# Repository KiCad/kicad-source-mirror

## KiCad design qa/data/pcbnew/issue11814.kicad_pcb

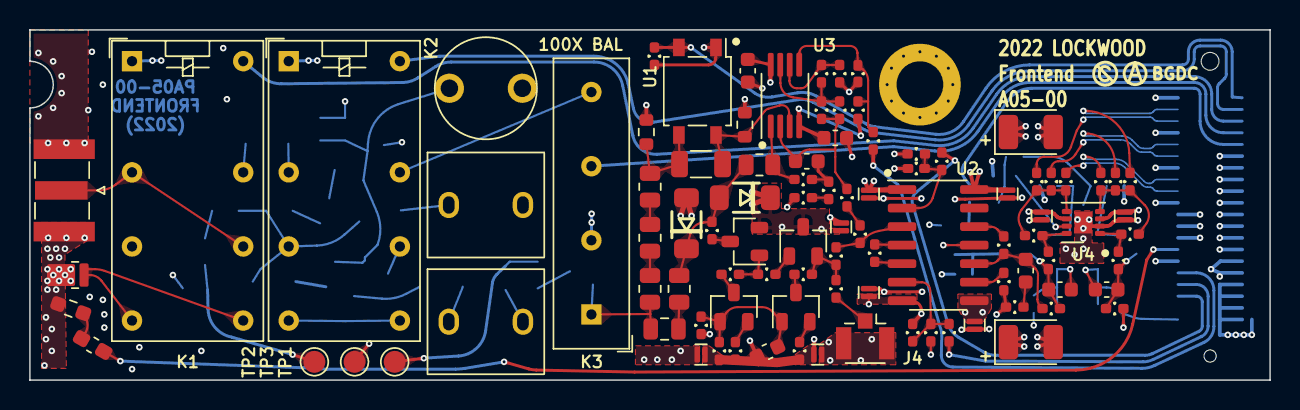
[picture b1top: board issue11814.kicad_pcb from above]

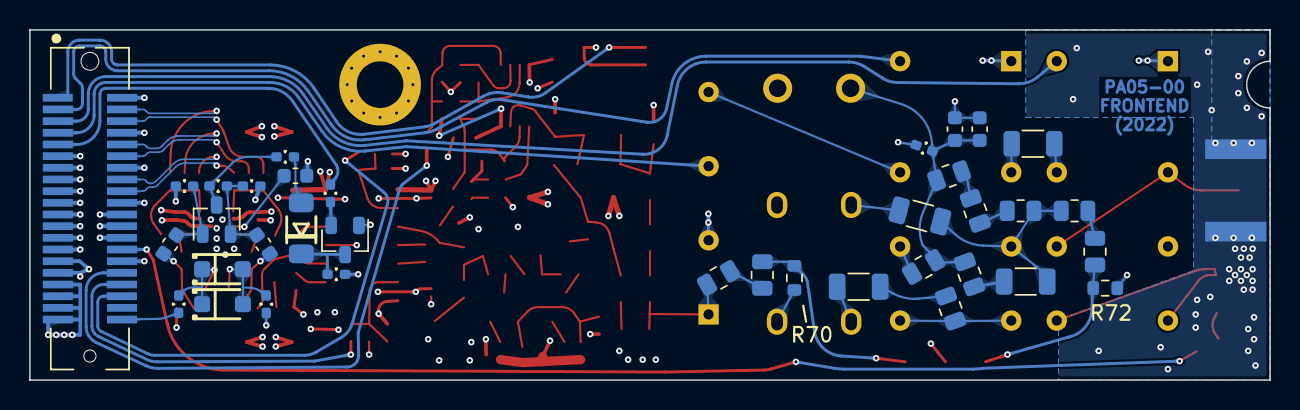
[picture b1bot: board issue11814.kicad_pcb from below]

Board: 4 copper layers, 85.0 x 24.0 mm, 133 parts (36 on the bottom side), 89 nets.

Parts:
C1, C7: 100n; C_0402_1005Metric_Pad0.74x0.62mm_HandSolder
C2, C4: 10p; C_1206_3216Metric
C3, C5: 2-18p; C-Trim-Vishay-BFC2-809-05
C6: 6p8; C_1206_3216Metric
C8: 15n; C_1206_3216Metric
C9: DNS; C_0603_1608Metric
C10: 560p; C_0603_1608Metric
C11: 62p; C_0603_1608Metric
C12, C18: 220p; C_0603_1608Metric
C13, C14: 47p; C_0603_1608Metric
C15: 15-60p; TrimCap-Generic
C16: 10n; C_0603_1608Metric
C17: 330p; C_0805_2012Metric
C19: 100p; C_0603_1608Metric
C28, C30: 47µ; CP_EIA-3528-15_AVX-H
C31, C32, C33: 100n; C_0603_1608Metric
CW1, CW2, CW3, CW4, CW5, CW6, CW7, CW8, CW9: 100n; C_0204_LowESL
D1, D5: 1N4007FL; D_SOD-123F
D2, D3, D4: LL4448; D_MiniMELF
FB1: 1k; L_0603_1608Metric_Pad1.05x0.95mm_HandSolder
H1: MountingHole_Pad; MountingHole_3.2mm_M3_DIN965_Pad
J1: Conn_Coaxial; SMA_Samtec_SMA-J-P-X-ST-EM1_EdgeMount
J3: INTERFACE; BergStak-Lite-40p-Receptacle
J4: TEST1; U.FL_Hirose_U.FL-R-SMT-1_Vertical
K1, K2: Relay-DPDT-CIT-J104D; Relay_DPDT_Omron_G5V-2
K3: Relay-SPST-Reed; Relay_SPST_StandexMeder_SIL_Form1A
Q1: MMBT3906; SOT-23
Q2: MMBFJ211; SOT-23
Q3: 2SK3557-7; SOT-23
Q4, Q5, Q6: MMBTH10; SOT-23
R1: 3k9; R_0402_1005Metric_Pad0.72x0.64mm_HandSolder
R2: 50; R_Susumu_HPT2012
R3, R5, R13: 30k; R_0402_1005Metric_Pad0.72x0.64mm_HandSolder
R7, R14: 120k; R_0402_1005Metric_Pad0.72x0.64mm_HandSolder
R8: 270; R_0402_1005Metric_Pad0.72x0.64mm_HandSolder
R9: 4R7; R_1206_3216Metric
R10: 18; R_0402_1005Metric_Pad0.72x0.64mm_HandSolder
R11: 18; R_0805_2012Metric
R12, R15, R18: 390k; R_0805_2012Metric
R16, R28: 390k; R_0603_1608Metric
R17, R51: 22; R_0805_2012Metric
R19, R24, R27: 330k; R_0805_2012Metric
R20, R54: 22; R_0402_1005Metric_Pad0.72x0.64mm_HandSolder
R21: 402; R_0402_1005Metric_Pad0.72x0.64mm_HandSolder
R22: 11k8; R_0402_1005Metric_Pad0.72x0.64mm_HandSolder
R23, R71, R74, R75: 3M; R_0805_2012Metric
R25, R37: DNS; R_0402_1005Metric_Pad0.72x0.64mm_HandSolder
R26: 100; R_0805_2012Metric
R29, R30, R44, R45: 30; R_0402_1005Metric_Pad0.72x0.64mm_HandSolder
R31: 3k3; R_0402_1005Metric_Pad0.72x0.64mm_HandSolder
R32: 430k; R_0402_1005Metric_Pad0.72x0.64mm_HandSolder
R33, R34, R38, R42, R46: 100k; R_0402_1005Metric_Pad0.72x0.64mm_HandSolder
R35: 390k; R_0402_1005Metric_Pad0.72x0.64mm_HandSolder
R36, R49: 2k4; R_0402_1005Metric_Pad0.72x0.64mm_HandSolder
R39: 240k; R_0402_1005Metric_Pad0.72x0.64mm_HandSolder
R40, R41: 10k; R_0402_1005Metric_Pad0.72x0.64mm_HandSolder
R43: 750k; R_0402_1005Metric_Pad0.72x0.64mm_HandSolder
R47: 4M7; R_0805_2012Metric
R48: 12k; R_0402_1005Metric_Pad0.72x0.64mm_HandSolder
R50: 51; R_0402_1005Metric_Pad0.72x0.64mm_HandSolder
R52, R53: 510; R_0402_1005Metric_Pad0.72x0.64mm_HandSolder
R55, R56, R59, R60, R62, R65, R68, R69: 47; R_0402_1005Metric_Pad0.72x0.64mm_HandSolder
R57, R66: 10; R_0402_1005Metric_Pad0.72x0.64mm_HandSolder
R58: 330; R_0402_1005Metric_Pad0.72x0.64mm_HandSolder
R61, R64: 1k; R_0402_1005Metric_Pad0.72x0.64mm_HandSolder
R63: 75; R_0402_1005Metric_Pad0.72x0.64mm_HandSolder
R67: 150; R_0402_1005Metric_Pad0.72x0.64mm_HandSolder
R70: SEL2; R_0603_1608Metric
R72: SEL1; R_0603_1608Metric
R73: 220k; R_0402_1005Metric_Pad0.72x0.64mm_HandSolder
TH1: 10k; R_0603_1608Metric_Pad0.98x0.95mm_HandSolder
TP1: SEL2; TestPoint_Pad_D1.5mm
TP2: SEL1; TestPoint_Pad_D1.5mm
TP3: SELG; TestPoint_Pad_D1.5mm
U1: AB30S; SO-4_4.4x4.3mm_P2.54mm
U2: VCA821ID; SOIC-14_3.9x8.7mm_P1.27mm
U3: ADA4177-2; MSOP-8_3x3mm_P0.65mm
U4: LMH6551MA; WSON-8-1EP_3x2.5mm_P0.5mm_EP1.2x1.5mm_PullBack

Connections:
+5V: C28.1, C32.1, CW1.1, CW2.1, CW3.1, CW4.1, D3.1 (K), J3.11, J3.12, J3.13, J3.14, Q3.2 (D), Q5.3 (C), R38.2, U2.1 (+V_{CC}), U2.14 (+V_{CC}), U3.8 (V+), U4.3 (V+)
+12V: J3.6, J3.7, J3.8, J3.9, K1.1, K2.1, K3.3, R73.1, U1.1 (A)
-5V: C19.2, C30.2, C33.1, CW5.1, CW6.1, CW7.1, CW8.1, CW9.1, D4.2 (A), J3.17, J3.18, J3.19, J3.20, R7.2, R14.2, R33.1, R41.2, R58.1, R61.1, R67.1, U2.7 (-V_{CC}), U2.8 (-V_{CC}), U3.4 (V-), U4.6 (V-)
/ATN_IN: C4.2, C6.1, K2.6, R12.1, R71.1
/EN_BWL: J3.5, R31.1
/LMH_EN: C31.1, U4.7 (EN)
/OFFSET1: J3.36, R13.2
/OFFSET2: J3.37, R5.2
/OUT1+: J3.22, R62.1
/OUT1-: J3.23, R65.1
/OUT2+: J3.25, R59.1
/OUT2-: J3.26, R60.1
/OUT3+: J3.28, R55.1
/OUT3-: J3.29, R56.1
/SIG_1X: K2.8, K2.9, R11.2
/SIG_1XC: C2.2, R11.1
/SIG_1XC2: C2.1, C3.1
/SIG_50: K1.8, K1.9, R2.1
/SIG_100X: C10.2, C11.2, C15.1, R17.2, R18.2, R22.2, R26.1
/SIG_100XC2: C4.1, C5.1
/SIG_100XD: K2.11, R26.2
/SIG_IN_{1}: J1.1 (In), K1.4, K1.11
/SIG_IN_{2}: K1.13, R9.1
/SIG_IN_{3}: K2.4, R9.2
/SIG_{1}: K2.13, K3.7
/SIG_{2}: C17.1, K3.1, R23.1, R27.2
/THERM: FB1.2, J3.34
/VFILT': C14.1, D1.1 (K), D5.1 (K), R34.2
/VFILTER: J3.40, R34.1
/VGAIN: J3.38, R1.1
/~EN_50: J3.3, K1.16
/~EN_ATN_1X: J3.2, K2.16
/~EN_DC: J3.1, R73.2, U1.2 (K)
/~EN_SIG: J3.4, K3.5
GND: C1.2, C3.2, C5.2, C7.2, C10.1, C11.1, C15.2, C28.2, C30.1, C31.2, C32.2, C33.2, CW1.2, CW2.2, CW3.2, CW4.2, CW5.2, CW6.2, CW7.2, CW8.2, CW9.2, H1.1, J1.2 (Ext), J3.10, J3.15, J3.16, J3.21, J3.24, J3.27, J3.30, J3.31, J3.32, J3.33, J3.35, J4.2 (Ext), Q1.1 (B), R2.2, R3.2, R8.2, R16.1, R20.1, R22.1, R25.1, R28.1, R30.1, R37.2, R46.1, R50.1, R64.2, R70.2, R72.2, TH1.2, TP3.1, U2.11 (GND), U4.2 (VCM), U4.9 (DAP)
unnamed: C1.1, R1.2, R3.1, U2.2 (V_{G})
unnamed: C6.2, R17.1
unnamed: C7.1, R13.1, R14.1, U3.5 (+)
unnamed: C8.1, R16.2, R19.1, U1.3 (D1)
unnamed: C8.2, R28.2, U1.4 (D2), U3.3 (+)
unnamed: C9.1, R21.2, R29.1, U2.10 (V_{OUT})
unnamed: C9.2, R25.2
unnamed: C12.1, C14.2, R30.2, R45.1
unnamed: C12.2, Q2.1 (S), R38.1
unnamed: C13.1, C18.2, R29.2, R44.1
unnamed: C13.2, D1.2 (A), D5.2 (A), R33.2
unnamed: C16.1, R32.1, R35.1, R39.2, U3.2 (-)
unnamed: C16.2, R48.1, R49.2
unnamed: C17.2, R51.2
unnamed: C18.1, Q2.2 (D), R42.1, R46.2
unnamed: C19.1, Q4.1 (B), Q6.1 (B), R61.2, R64.1
unnamed: D2.1 (K), Q1.3 (C), R41.1
unnamed: D2.2 (A), R40.2
unnamed: D3.2 (A), D4.1 (K), R47.2, R51.1, R54.2
unnamed: FB1.1, TH1.1
unnamed: J4.1 (In), R68.2
unnamed: Q1.2 (E), R31.2
unnamed: Q2.3 (G), R40.1, R42.2
unnamed: Q3.1 (S), R57.2, R63.1
unnamed: Q3.3 (G), R54.1
unnamed: Q4.2 (E), R58.2
unnamed: Q4.3 (C), R57.1
unnamed: Q5.1 (B), R63.2
unnamed: Q5.2 (E), R66.2, R68.1, R69.1
unnamed: Q6.2 (E), R67.2
unnamed: Q6.3 (C), R66.1
unnamed: R5.1, R7.1, R8.1, U2.6 (-V_{IN})
unnamed: R10.1, U2.4 (+R_{G})
unnamed: R10.2, U2.5 (-R_{G})
unnamed: R12.2, R15.1
unnamed: R15.2, R18.1
unnamed: R19.2, R24.1
unnamed: R20.2, U2.9 (V_{REF})
unnamed: R21.1, U2.12 (FB)
unnamed: R23.2, R74.1
unnamed: R24.2, R27.1
unnamed: R32.2, R35.2, R36.1, U3.7
unnamed: R36.2, R37.1, U3.6 (-)
unnamed: R39.1, R43.2
unnamed: R43.1, R69.2, U2.3 (+V_{IN})
unnamed: R44.2, R52.1, U4.8 (+)
unnamed: R45.2, R53.1, U4.1 (-)
unnamed: R47.1, R48.2, U3.1
unnamed: R49.1, R50.2
unnamed: R52.2, R56.2, R60.2, R65.2, U4.5 (-)
unnamed: R53.2, R55.2, R59.2, R62.2, U4.4 (+)
unnamed: R70.1, R74.2, TP1.1
unnamed: R71.2, R75.1
unnamed: R72.1, R75.2, TP2.1

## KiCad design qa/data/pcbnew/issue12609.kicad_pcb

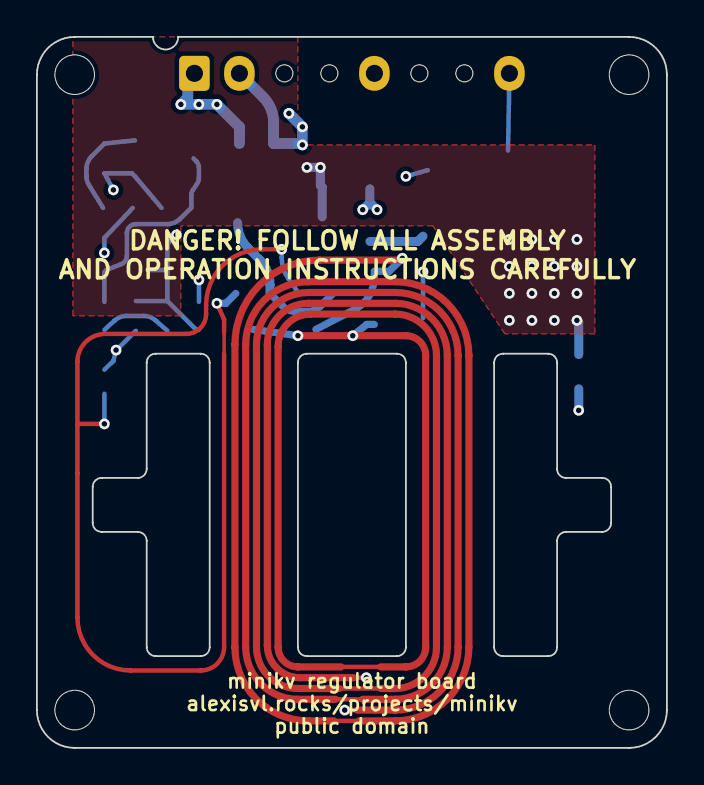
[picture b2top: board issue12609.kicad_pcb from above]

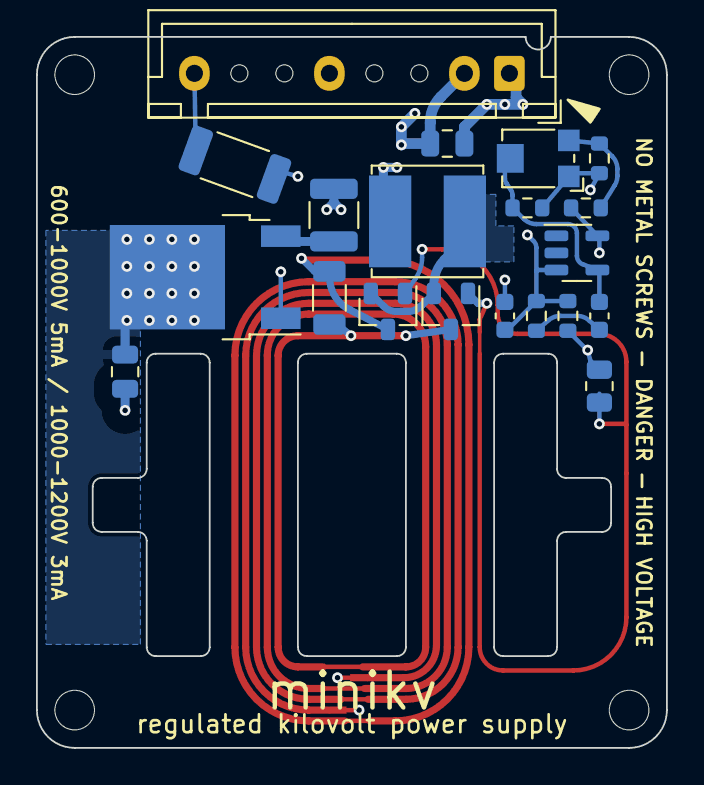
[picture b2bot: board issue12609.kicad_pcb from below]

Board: 4 copper layers, 35.0 x 39.5 mm, 27 parts (20 on the bottom side), 15 nets.

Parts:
C1: 15n; C_1206_3216Metric
C2, C3: 1u; C_0805_2012Metric
C4: 390p; C_0603_1608Metric
C5: 220n; C_0603_1608Metric
H1, H2, H3, H4: MountingHole; MountingHole_2.2mm_M2
J1: Conn_01x08; JST_XH_B8B-XH-A_1x08_P2.50mm_Vertical
L1: 220u; L_Bourns_SRN6045TA
Q1, Q2: PBSS8110; SOT-23
Q3: PJD25N03; TO-252-2
R1: 10M; R_2010_5025Metric
R2, R6: 15k; R_0603_1608Metric
R3: 9k1; R_0603_1608Metric
R4: 100k; R_0603_1608Metric
R5: 3M3; R_0603_1608Metric
R7: 1k; R_0805_2012Metric
R8: 1r; R_1210_3225Metric
RV1: 100k; Potentiometer_Bourns_TC33X_Vertical
TW1, TW2: 2½T; NetTie-0.4mm
TW3: ½T; NetTie-0.2mm-1mmClear
U1: TLV431; SOT-23-5

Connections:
+12V: C2.1, C3.1, J1.1, R6.1, R7.1, TW1.2, TW2.1
/1kV: J1.8, R1.1
/RoyerReg: C3.2, L1.2, Q3.2 (D)
GND: C2.2, C5.2, J1.2, R3.2, R8.2, U1.5 (A)
unnamed: C4.2, R5.1
unnamed: Q1.1 (B), R7.2, TW3.1
unnamed: C1.1, Q1.3 (C), TW1.1
unnamed: L1.1, Q1.2 (E), Q2.2 (E)
unnamed: Q2.1 (B), TW3.2
unnamed: C1.2, Q2.3 (C), TW2.2
unnamed: C5.1, Q3.1 (G), R5.2, R6.2, U1.3 (K)
unnamed: Q3.3 (S), R8.1
unnamed: R2.2, R3.1, RV1.3
unnamed: R1.2, R2.1, R4.1, RV1.1
unnamed: C4.1, R4.2, RV1.2, U1.4 (R)

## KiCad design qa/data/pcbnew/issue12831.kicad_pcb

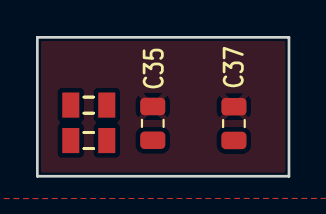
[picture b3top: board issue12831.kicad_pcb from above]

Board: 2 copper layers, 14.0 x 7.7 mm, 4 parts (0 on the bottom side), 2 nets, no tracks yet.

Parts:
C35: 1µ; C_0805_2012Metric_60
C37: 10N; C_0805_2012Metric_60
L1, L6: FB60E; INDC2012X90

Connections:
/-5V: C35.1, C37.1, L6.2
GND: C35.2, C37.2

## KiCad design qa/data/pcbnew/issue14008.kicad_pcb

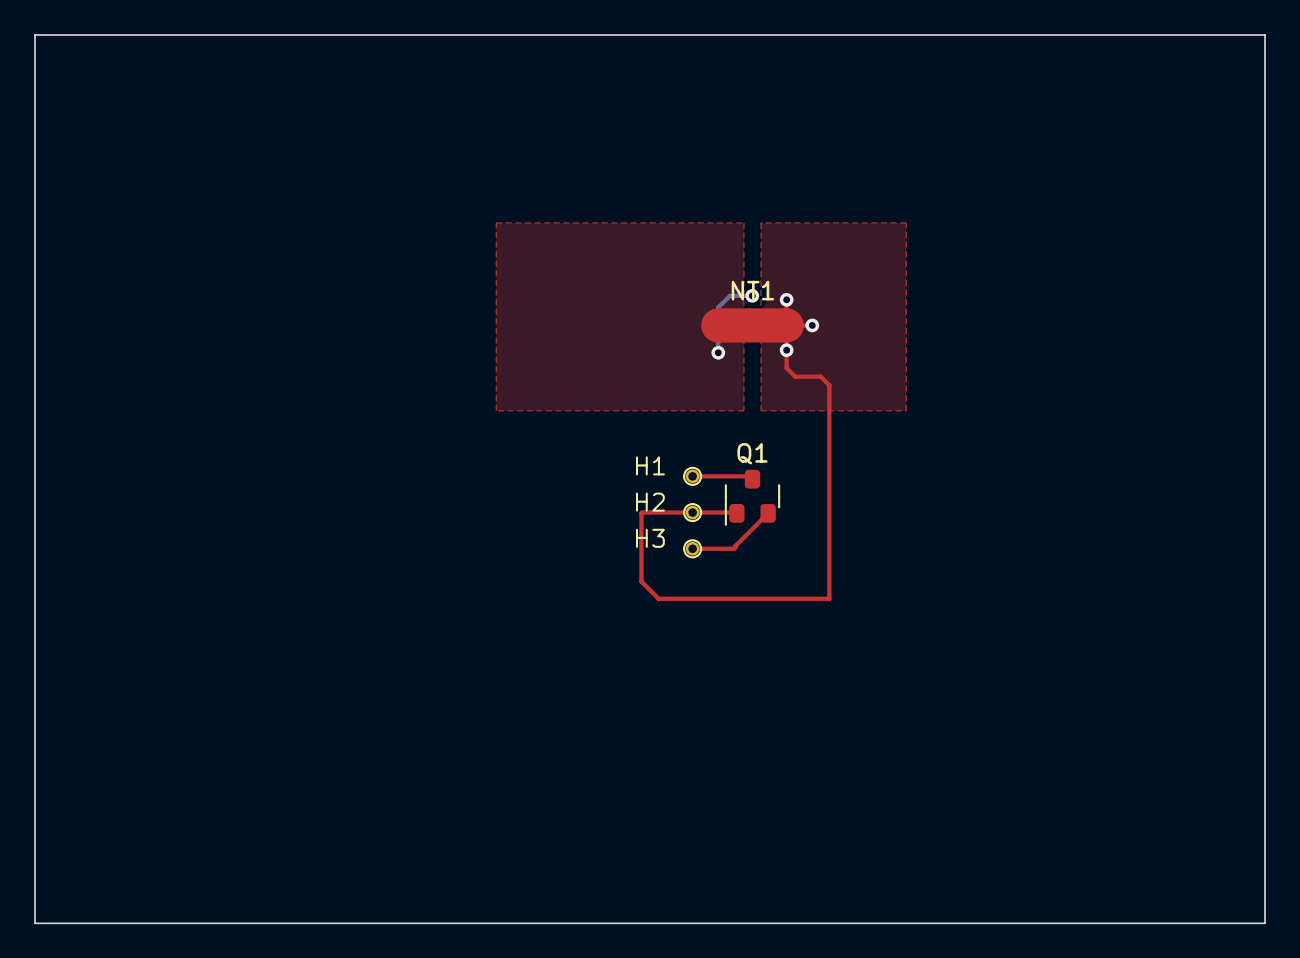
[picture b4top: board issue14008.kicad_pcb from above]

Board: 2 copper layers, 72.0 x 52.0 mm, 5 parts (0 on the bottom side), 3 nets.

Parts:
H1, H2, H3: MountingHole_Pad; TestPoint_THTPad_1.0mm_Drill_0.6mm
NT1: Net-Tie_2; NetTie-2_SMD_Pad2.0mm
Q1: DMP3098L-7-ALPHA; SOT-23-Alpha

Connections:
/BATT_+: H1.1, Q1.D
/BATT_PROT: H3.1, Q1.S
GND: H2.1, NT1.2, Q1.G

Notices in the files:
qa/data/pcbnew/issue12609.kicad_pcb:
public domain
